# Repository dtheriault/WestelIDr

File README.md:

# WestelIDr
Westel Repeater Controller

This repository contains eagle files and arduino sketch files supporting a repeater
controller based on a Teensy3.2 chip.

The hardware was originally designed to support a Westel DRB25 repeater for WB7NFX
and then updated to support the K7YCA ARES/RACES team who also had one of these
machines.  The controller hardware while supporting the Westel repeater should be
easily modified for other repeater types.  It requires +12v @ approx 150ma, PTT,
Microphone and line audio to generate simple software based carrier detect.

The controller will generate a CW ID or Voice ID in the latest revision of the
sketch file for k7yca.  Can be operated in Ham or Commercial mode with different
timeouts.

Eagle files contain schematics and PCB layout supporting a 3 channel mixer and 3
transistor simplistic audio amplifier to drive a speaker mounted on the Westel
repeater.  There's Gerber files available to spin your own board.

NOTE IMPORTANT:  Current major pin-out issue with the voice ID chip.  I'll update
files and new layout once I fix the darn chip library file.

There's also some mechanical files for a mounting plate for the Westel repeater
which were contributed by Rob KG7LMI.

CW ID code was made possible by SV1DJG and very much appreciated for allowing me to
include his software in the sketch files.

For latest software please refer to the Sketch/k7yca/k7yca.ino file as this version
matches the hardware.  The other two versions were for earlier revisions of the
board for WB7NFX and our Sheriff's Jeep Posse team where I used the controller in
an AmmoCan portable repeater I built for them.

Contact info:

email:  no1d.doug@gmail.com
repository:  https://github.com/dtheriault/WestelIDr

 License:

 Copyright (C) 2017 Douglas Theriault - NO1D

 Software is free software: you can redistribute it and/or modify
 it under the terms of the GNU General Public License as published by
 the Free Software Foundation, either version 3 of the License, or
 (at your option) any later version.

 This is distributed in the hope that it will be useful to someone or ham club/group,
 but WITHOUT ANY WARRANTY; without even the implied warranty of MERCHANTABILITY
 or FITNESS FOR A PARTICULAR PURPOSE.  See the GNU General Public License for
 more details.

 You should have received a copy of the GNU General Public License
 in the repository.  If not, see <http://www.gnu.org/licenses/>.

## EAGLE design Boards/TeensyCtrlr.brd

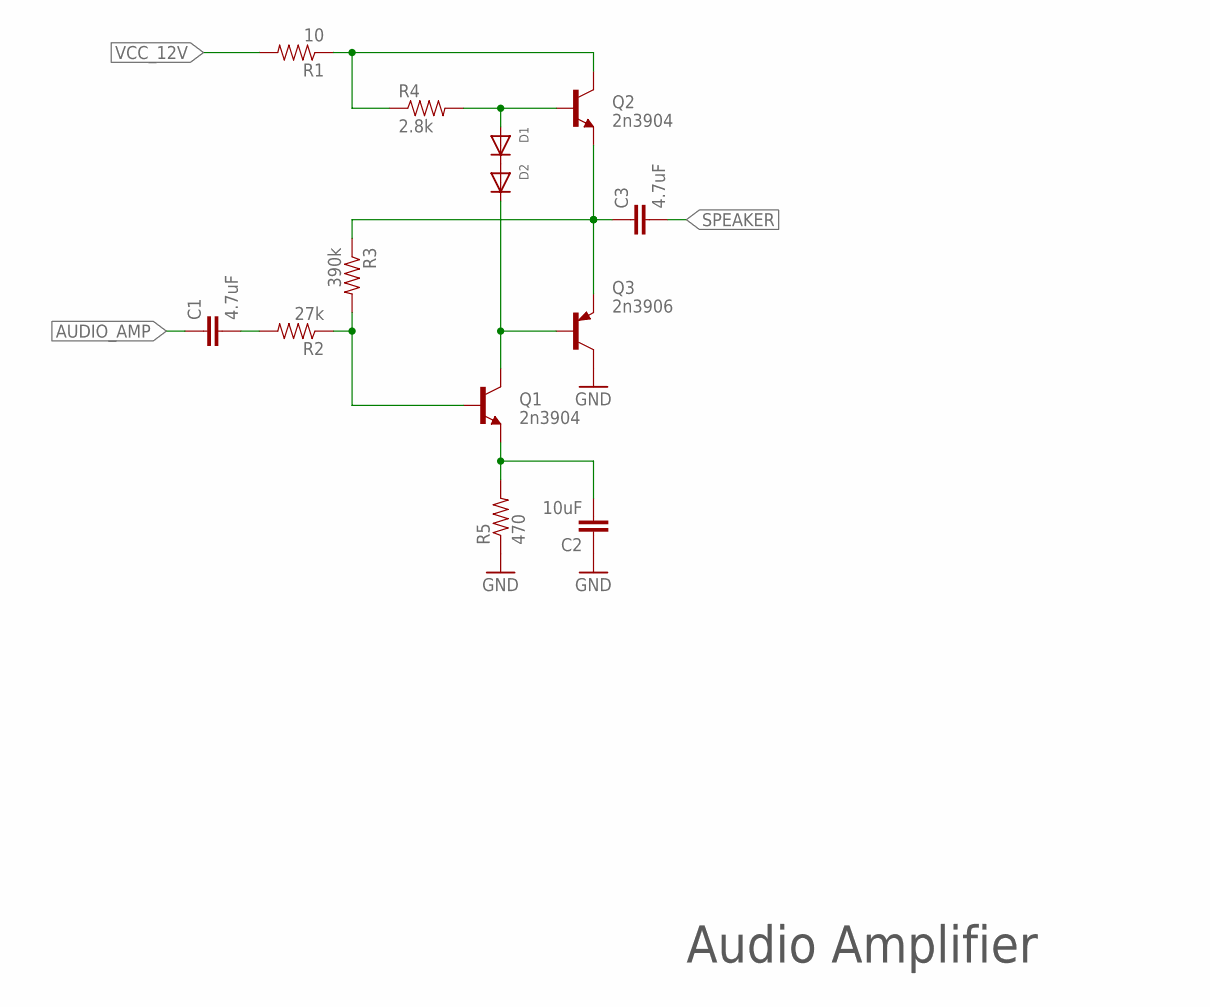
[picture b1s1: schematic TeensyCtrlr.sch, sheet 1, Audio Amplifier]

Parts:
C1, C3: 4.7uF; CAP-PTH-SMALL
C2: 10uF; CAP-PTH-SMALL
D1, D2: DIODEDO-1N4148; DO-1N4148
Q1, Q2: 2n3904; TO-92-AMMO
Q3: 2n3906; TO92-EBC
R1: 10; 0805
R2: 27k; 0805
R3: 390k; 0805
R4: 2.8k; 0805
R5: 470; 0805

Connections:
AUDIO_AMP: C1.1; also elsewhere on the board
GND: C2.1, Q3.C, R5.1; also elsewhere on the board
unnamed: C1.2, R2.2
unnamed: Q2.3 (C), R1.1, R4.1
unnamed: C2.2, Q1.1 (E), R5.2
unnamed: C3.1, Q2.1 (E), Q3.E, R3.1
unnamed: D1.C, D2.A
unnamed: D1.A, Q2.2 (B), R4.2
unnamed: D2.C, Q1.3 (C), Q3.B
unnamed: Q1.2 (B), R2.1, R3.2
SPEAKER: C3.2; also elsewhere on the board
VCC_12V: R1.2; also elsewhere on the board

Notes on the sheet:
Audio Amplifier

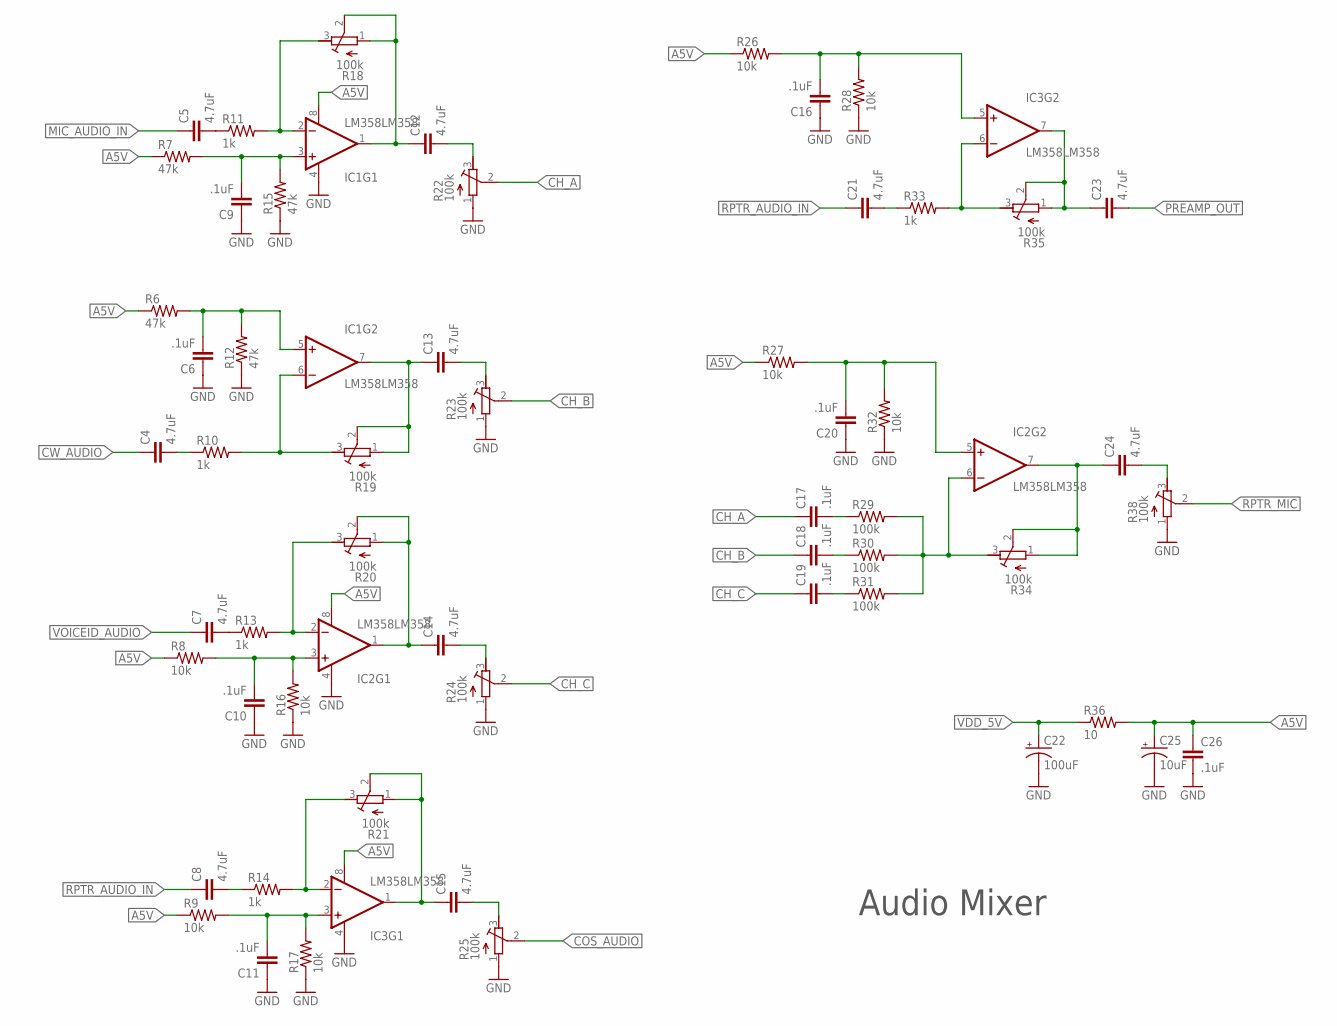
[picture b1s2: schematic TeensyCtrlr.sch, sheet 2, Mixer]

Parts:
C4, C5, C7, C8, C12, C13, C14, C15, C21, C23, C24: 4.7uF; CAP-PTH-SMALL2
C6, C9, C10, C11, C16, C17, C18, C19, C20, C26: .1uF; 0805
C22: 100uF; CPOL-RADIAL-10UF-25V
C25: 10uF; CPOL-RADIAL-100UF-25V
IC1, IC2, IC3: LM358LM358; SOIC8
R6, R7, R12, R15: 47k; 0805
R8, R9, R16, R17, R26, R27, R28, R32: 10k; 0805
R10, R11, R13, R14, R33: 1k; 0805
R18, R19, R20, R21, R22, R23, R24, R25, R34, R35, R38: 100k; RTRIM3296X
R29, R30, R31: 100k; 0805
R36: 10; 0805

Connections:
A5V: C25.1 (+), C26.1, IC1.8 (V+), IC2.8 (V+), IC3.8 (V+), R6.1, R7.1, R8.1, R9.1, R26.1, R27.1, R36.2
CH_A: C17.1, R22.2 (S)
CH_B: C18.1, R23.2 (S)
CH_C: C19.1, R24.2 (S)
COS_AUDIO: R25.2 (S); also elsewhere on the board
CW_AUDIO: C4.1; also elsewhere on the board
GND: C6.1, C9.1, C10.1, C11.1, C16.1, C20.1, C22.2 (-), C25.2 (-), C26.2, IC1.4 (V-), IC2.4 (V-), IC3.4 (V-), R12.1, R15.1, R16.1, R17.1, R22.1 (A), R23.1 (A), R24.1 (A), R25.1 (A), R28.1, R32.1, R38.1 (A); also elsewhere on the board
MIC_AUDIO_IN: C5.1; also elsewhere on the board
unnamed: IC1.2 (-IN), R11.2, R18.3 (E)
unnamed: C9.2, IC1.3 (+IN), R7.2, R15.2
unnamed: C5.2, R11.1
unnamed: C12.1, IC1.1 (OUT), R18.1 (A), R18.2 (S)
unnamed: C12.2, R22.3 (E)
unnamed: IC1.6 (-IN), R10.2, R19.3 (E)
unnamed: C6.2, IC1.5 (+IN), R6.2, R12.2
unnamed: C4.2, R10.1
unnamed: C13.1, IC1.7 (OUT), R19.1 (A), R19.2 (S)
unnamed: C13.2, R23.3 (E)
unnamed: IC2.2 (-IN), R13.2, R20.3 (E)
unnamed: C10.2, IC2.3 (+IN), R8.2, R16.2
unnamed: C7.2, R13.1
unnamed: C14.1, IC2.1 (OUT), R20.1 (A), R20.2 (S)
unnamed: C14.2, R24.3 (E)
unnamed: IC2.6 (-IN), R29.2, R30.2, R31.2, R34.3 (E)
unnamed: C20.2, IC2.5 (+IN), R27.2, R32.2
unnamed: C24.1, IC2.7 (OUT), R34.1 (A), R34.2 (S)
unnamed: C24.2, R38.3 (E)
unnamed: IC3.2 (-IN), R14.2, R21.3 (E)
unnamed: C11.2, IC3.3 (+IN), R9.2, R17.2
unnamed: C8.2, R14.1
unnamed: C15.1, IC3.1 (OUT), R21.1 (A), R21.2 (S)
unnamed: C15.2, R25.3 (E)
unnamed: IC3.6 (-IN), R33.2, R35.3 (E)
unnamed: C16.2, IC3.5 (+IN), R26.2, R28.2
unnamed: C21.2, R33.1
unnamed: C23.1, IC3.7 (OUT), R35.1 (A), R35.2 (S)
unnamed: C17.2, R29.1
unnamed: C18.2, R30.1
unnamed: C19.2, R31.1
PREAMP_OUT: C23.2; also elsewhere on the board
RPTR_AUDIO_IN: C8.1, C21.1; also elsewhere on the board
RPTR_MIC: R38.2 (S); also elsewhere on the board
VDD_5V: C22.1 (+), R36.1; also elsewhere on the board
VOICEID_AUDIO: C7.1; also elsewhere on the board

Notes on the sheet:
Audio Mixer

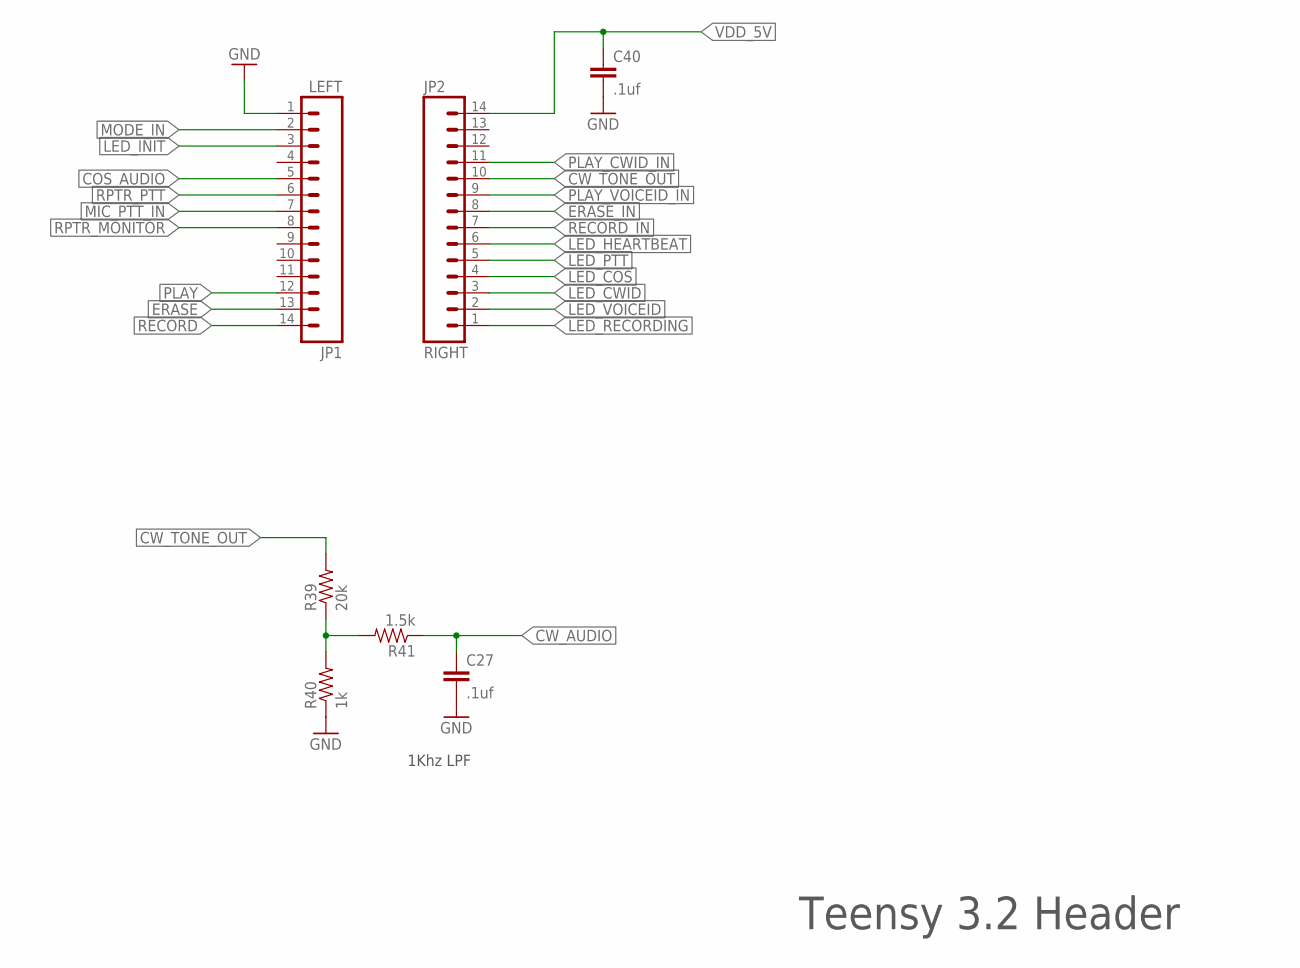
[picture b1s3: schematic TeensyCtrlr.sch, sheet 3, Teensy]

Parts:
C27, C40: .1uf; 0805
JP1: LEFT; 1X14-LONGPADS
JP2: RIGHT; 1X14-LONGPADS
R39: 20k; 0805
R40: 1k; 0805
R41: 1.5k; 0805

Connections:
COS_AUDIO: JP1.5; also elsewhere on the board
CW_AUDIO: C27.1, R41.1; also elsewhere on the board
CW_TONE_OUT: JP2.10, R39.2
ERASE: JP1.13; also elsewhere on the board
ERASE_IN: JP2.8; also elsewhere on the board
GND: C27.2, C40.2, JP1.1, R40.1; also elsewhere on the board
LED_COS: JP2.4; also elsewhere on the board
LED_CWID: JP2.3; also elsewhere on the board
LED_HEARTBEAT: JP2.6; also elsewhere on the board
LED_INIT: JP1.3; also elsewhere on the board
LED_PTT: JP2.5; also elsewhere on the board
LED_RECORDING: JP2.1; also elsewhere on the board
LED_VOICEID: JP2.2; also elsewhere on the board
MIC_PTT_IN: JP1.7; also elsewhere on the board
MODE_IN: JP1.2; also elsewhere on the board
unnamed: R39.1, R40.2, R41.2
PLAY: JP1.12; also elsewhere on the board
PLAY_CWID_IN: JP2.11; also elsewhere on the board
PLAY_VOICEID_IN: JP2.9; also elsewhere on the board
RECORD: JP1.14; also elsewhere on the board
RECORD_IN: JP2.7; also elsewhere on the board
RPTR_MONITOR: JP1.8; also elsewhere on the board
RPTR_PTT: JP1.6; also elsewhere on the board
VDD_5V: C40.1, JP2.14; also elsewhere on the board

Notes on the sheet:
Teensy 3.2 Header
1Khz LPF

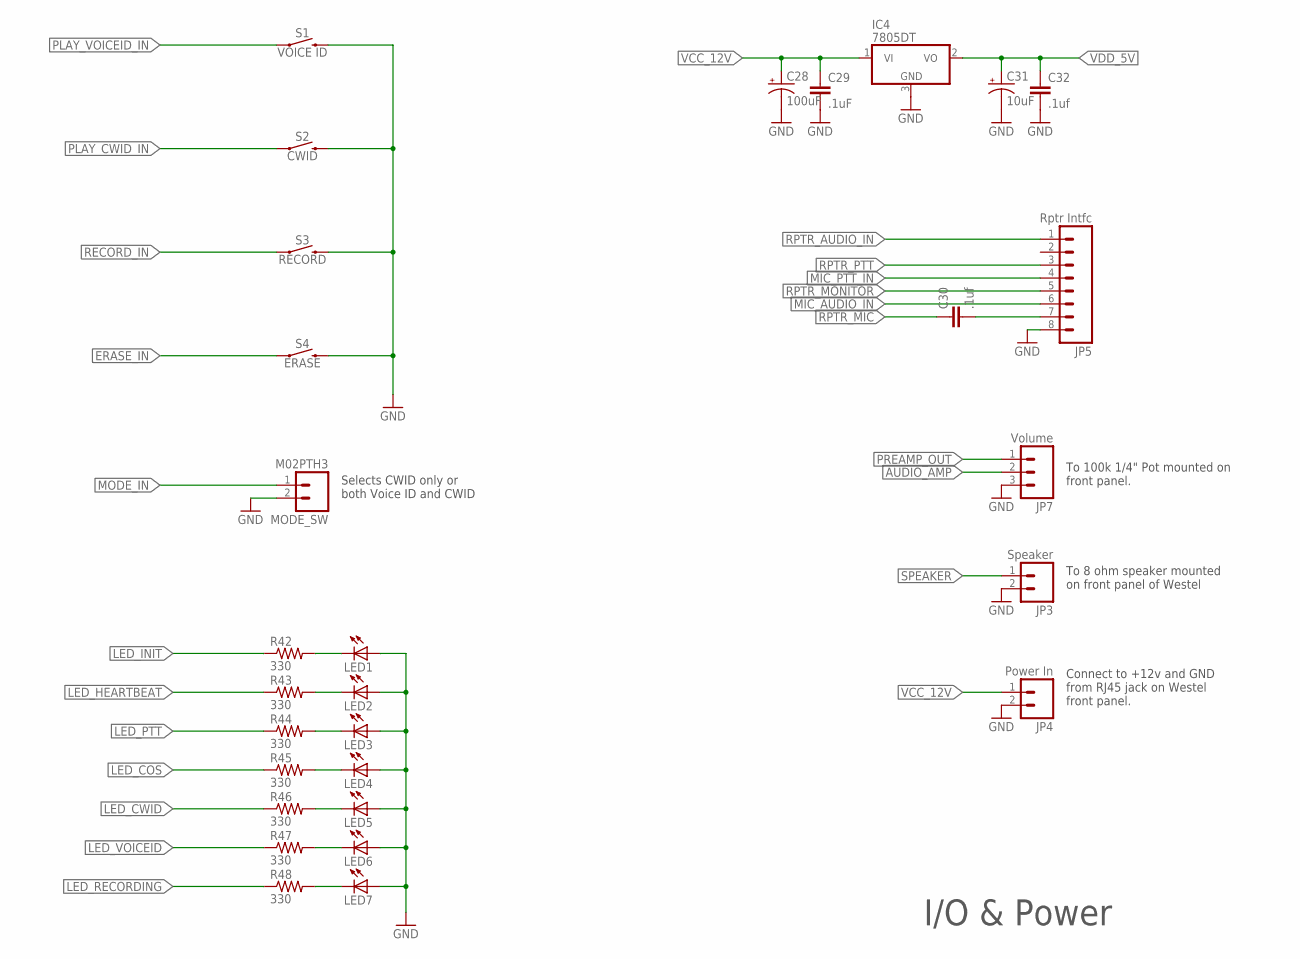
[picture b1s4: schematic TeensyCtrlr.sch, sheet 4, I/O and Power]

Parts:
C28: 100uF; CPOL-RADIAL-1000UF-25V
C29: .1uF; 0805
C30, C32: .1uf; 0805
C31: 10uF; CPOL-RADIAL-100UF-25V
IC4: 7805DT; TO252
JP3: Speaker; 1X02_LONGPADS
JP4: Power In; 1X02_LONGPADS
JP5: Rptr Intfc; 1X08_LONGPADS
JP7: Volume; 1X03_LONGPADS
LED1, LED2, LED3, LED4, LED5, LED6, LED7: LED5MM
MODE_SW: M02PTH3; 1X02_LONGPADS
R42, R43, R44, R45, R46, R47, R48: 330; 0805
S1: VOICE ID; TACTILE_SWITCH_PTH_6.0MM
S2: CWID; TACTILE_SWITCH_PTH_6.0MM
S3: RECORD; TACTILE_SWITCH_PTH_6.0MM
S4: ERASE; TACTILE_SWITCH_PTH_6.0MM

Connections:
AUDIO_AMP: JP7.2; also elsewhere on the board
ERASE_IN: S4.1; also elsewhere on the board
GND: C28.-, C29.2, C31.2 (-), C32.2, IC4.3 (GND), JP3.2, JP4.2, JP5.8, JP7.3, LED1.A, LED2.A, LED3.A, LED4.A, LED5.A, LED6.A, LED7.A, MODE_SW.2, S1.3 (2), S2.3 (2), S3.3 (2), S4.3 (2); also elsewhere on the board
LED_COS: R45.1; also elsewhere on the board
LED_CWID: R46.1; also elsewhere on the board
LED_HEARTBEAT: R43.1; also elsewhere on the board
LED_INIT: R42.1; also elsewhere on the board
LED_PTT: R44.1; also elsewhere on the board
LED_RECORDING: R48.1; also elsewhere on the board
LED_VOICEID: R47.1; also elsewhere on the board
MIC_AUDIO_IN: JP5.6; also elsewhere on the board
MIC_PTT_IN: JP5.4; also elsewhere on the board
MODE_IN: MODE_SW.1; also elsewhere on the board
unnamed: LED1.K (C), R42.2
unnamed: LED2.K (C), R43.2
unnamed: LED3.K (C), R44.2
unnamed: LED4.K (C), R45.2
unnamed: LED5.K (C), R46.2
unnamed: LED6.K (C), R47.2
unnamed: LED7.K (C), R48.2
unnamed: C30.2, JP5.7
PLAY_CWID_IN: S2.1; also elsewhere on the board
PLAY_VOICEID_IN: S1.1; also elsewhere on the board
PREAMP_OUT: JP7.1; also elsewhere on the board
RECORD_IN: S3.1; also elsewhere on the board
RPTR_AUDIO_IN: JP5.1; also elsewhere on the board
RPTR_MIC: C30.1; also elsewhere on the board
RPTR_MONITOR: JP5.5; also elsewhere on the board
RPTR_PTT: JP5.3; also elsewhere on the board
SPEAKER: JP3.1; also elsewhere on the board
VCC_12V: C28.+, C29.1, IC4.1 (VI), JP4.1; also elsewhere on the board
VDD_5V: C31.1 (+), C32.1, IC4.2 (VO); also elsewhere on the board

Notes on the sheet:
I/O & Power
To 100k 1/4" Pot mounted on front panel.
To 8 ohm speaker mounted on front panel of Westel
Connect to +12v and GND from RJ45 jack on Westel front panel.
Selects CWID only or both Voice ID and CWID

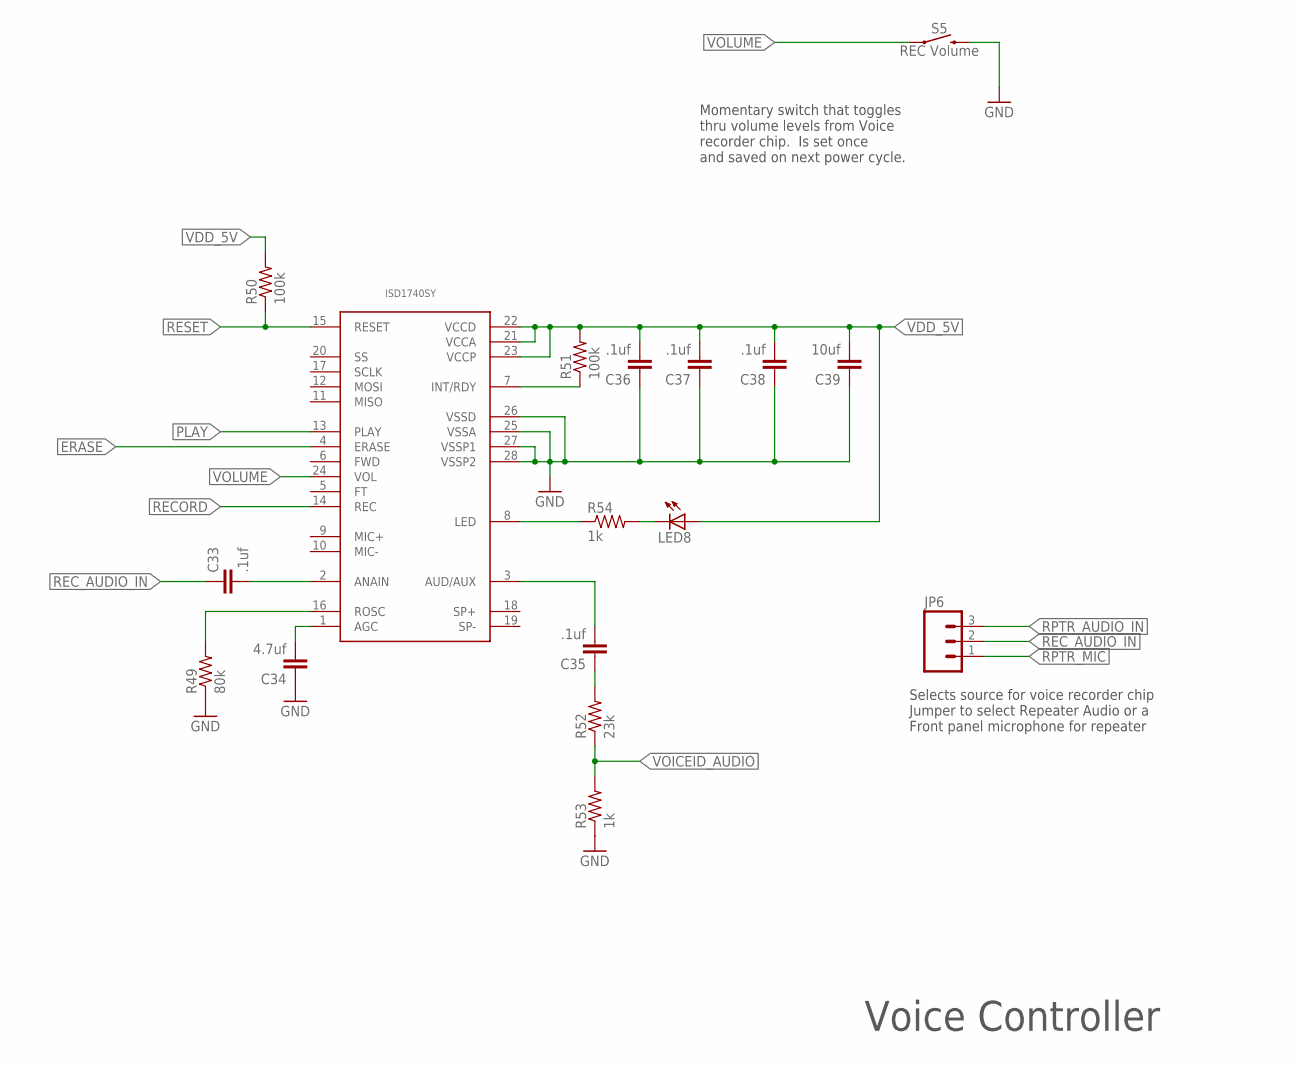
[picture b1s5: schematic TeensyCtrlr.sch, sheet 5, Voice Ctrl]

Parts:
C33, C35, C36, C37, C38: .1uf; 0805
C34: 4.7uf; 0805
C39: 10uf; 0805
IC$1: ISD1740SYSOIC28; SOIC-28
JP6: M03LONGPADS; 1X03_LONGPADS
LED8: LEDCHIP-LED0805; CHIP-LED0805
R49: 80k; 0805
R50, R51: 100k; 0805
R52: 23k; 0805
R53, R54: 1k; 0805
S5: REC Volume; TACTILE_SWITCH_PTH_6.0MM

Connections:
ERASE: IC$1.4 (ERASE); also elsewhere on the board
GND: C34.1, C36.1, C37.1, C38.1, C39.1, IC$1.25 (VSSA), IC$1.26 (VSSD), IC$1.27 (VSSP1), IC$1.28 (VSSP2), R49.1, R53.1, S5.3 (2); also elsewhere on the board
unnamed: C33.2, IC$1.2 (ANAIN)
unnamed: C35.2, IC$1.3 (AUD/AUX)
unnamed: C35.1, R52.2
unnamed: C34.2, IC$1.1 (AGC)
unnamed: IC$1.16 (ROSC), R49.2
unnamed: IC$1.7 (INT/RDY), R51.1
unnamed: IC$1.8 (LED), R54.1
unnamed: LED8.C, R54.2
PLAY: IC$1.13 (PLAY); also elsewhere on the board
RECORD: IC$1.14 (REC); also elsewhere on the board
REC_AUDIO_IN: C33.1, JP6.2
RESET: IC$1.15 (RESET), R50.1
RPTR_AUDIO_IN: JP6.3; also elsewhere on the board
RPTR_MIC: JP6.1; also elsewhere on the board
VDD_5V: C36.2, C37.2, C38.2, C39.2, IC$1.21 (VCCA), IC$1.22 (VCCD), IC$1.23 (VCCP), LED8.A, R50.2, R51.2; also elsewhere on the board
VOICEID_AUDIO: R52.1, R53.2; also elsewhere on the board
VOLUME: IC$1.24 (VOL), S5.1

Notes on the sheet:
Voice Controller
Selects source for voice recorder chip Jumper to select Repeater Audio or a Front panel microphone for repeater
Momentary switch that toggles thru volume levels from Voice recorder chip. Is set once and saved on next power cycle.

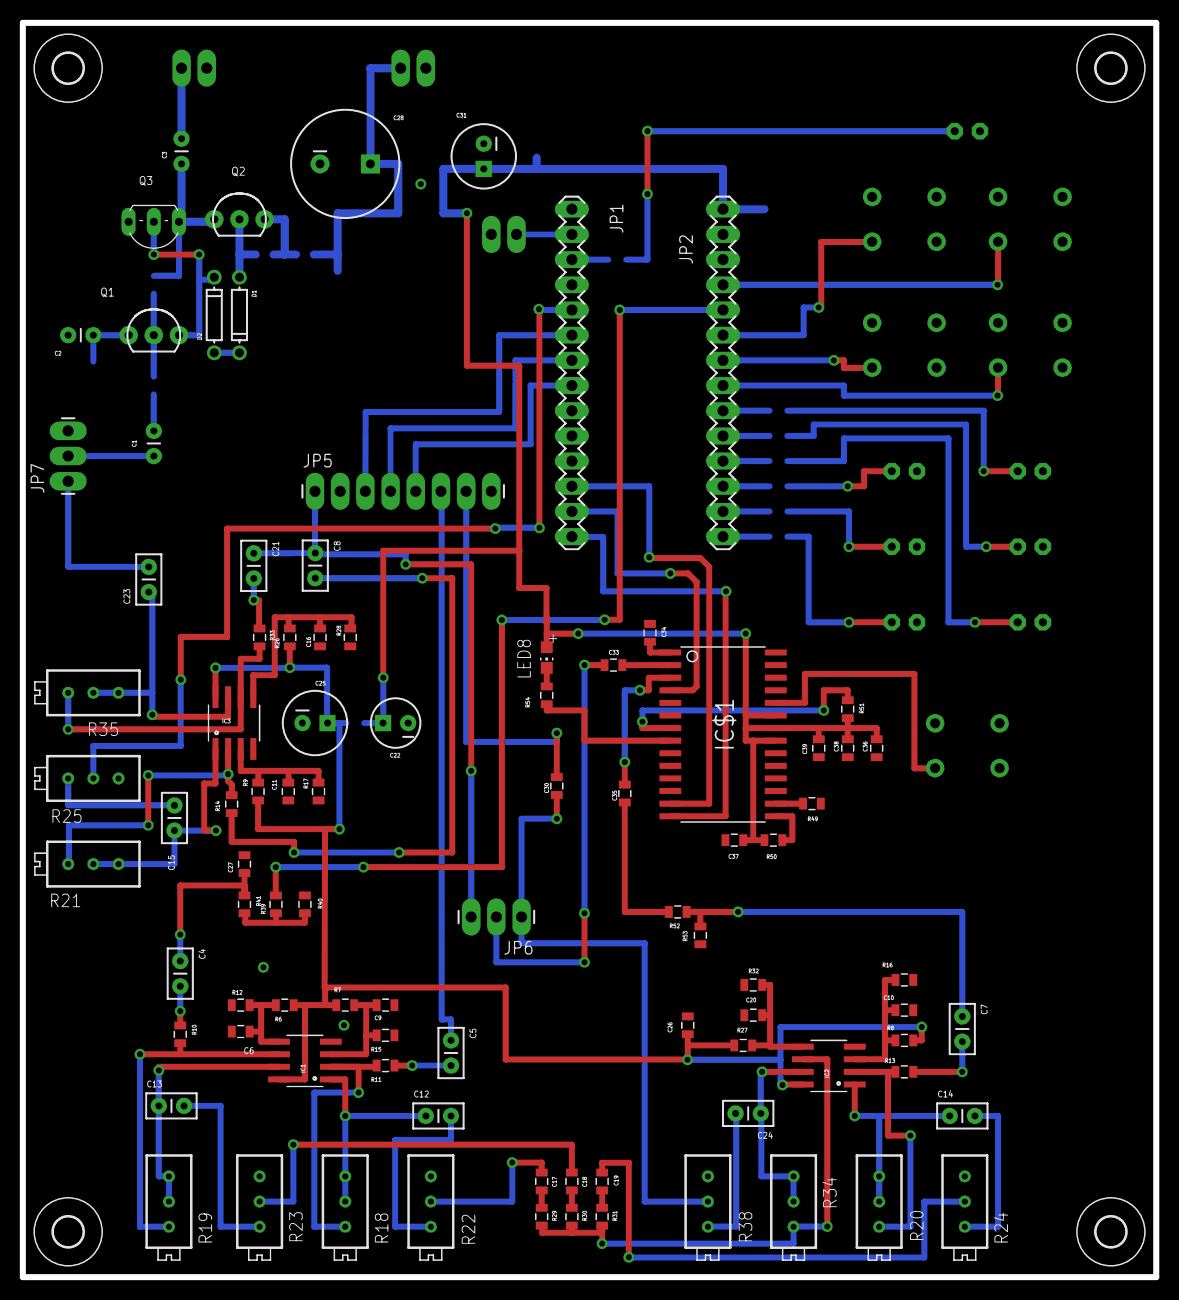
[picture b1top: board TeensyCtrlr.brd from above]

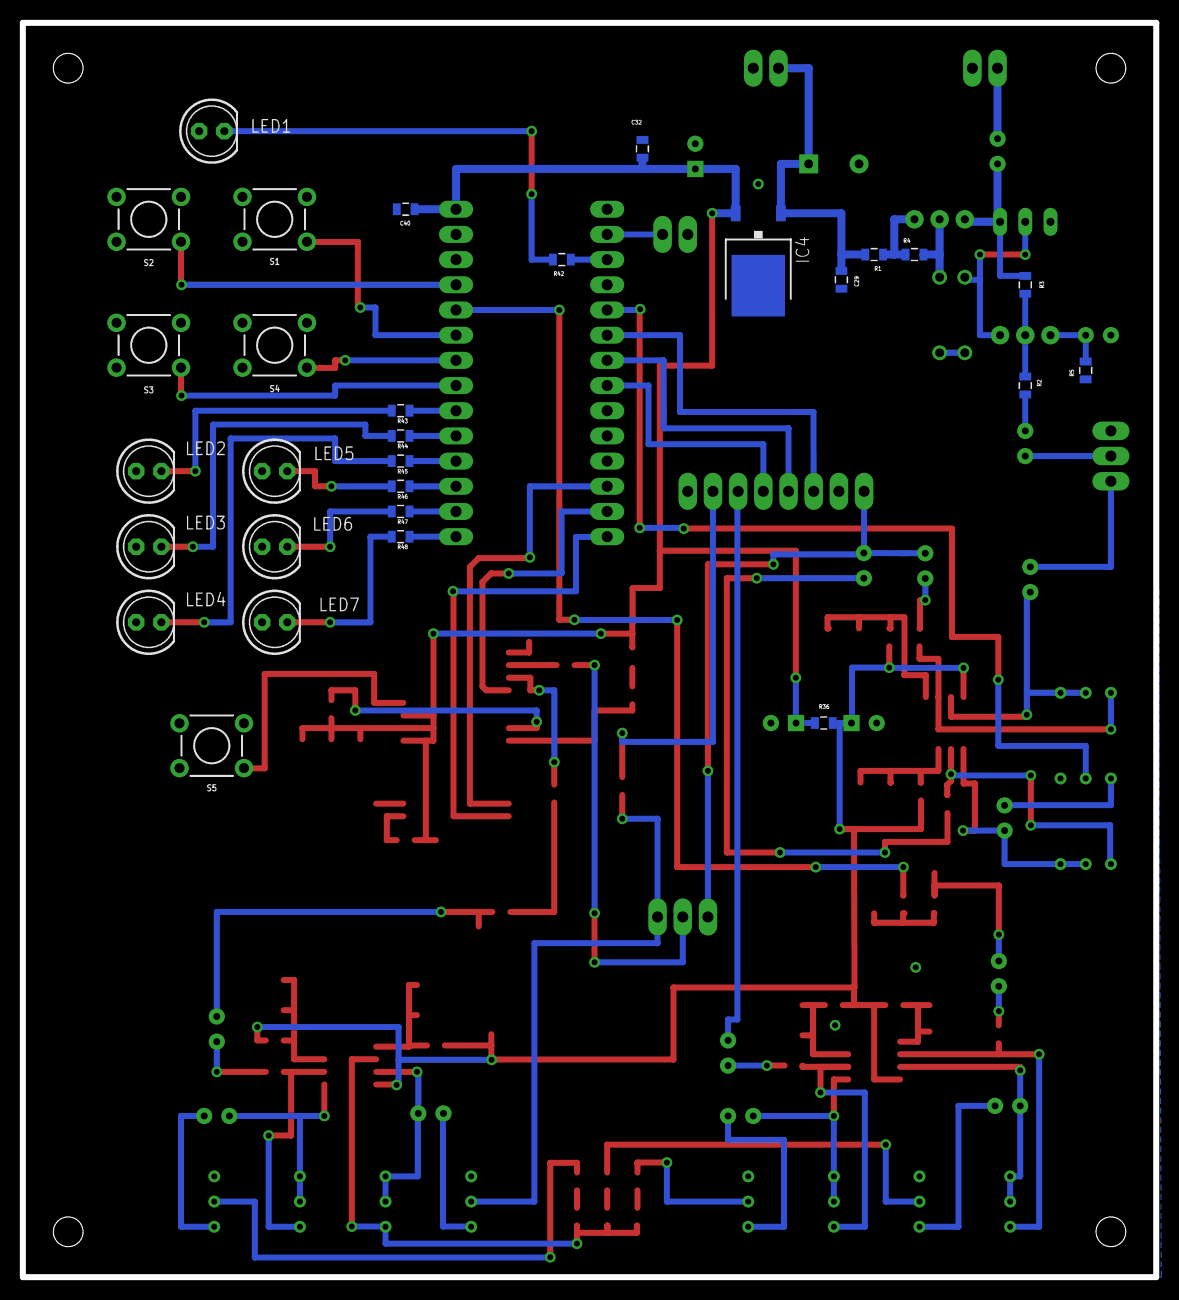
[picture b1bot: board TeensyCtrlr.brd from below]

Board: 2 copper layers, 114.3 x 126.5 mm, 128 parts (29 on the bottom side), 94 nets.

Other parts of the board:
U$1, U$2, U$3, U$4: 3,0

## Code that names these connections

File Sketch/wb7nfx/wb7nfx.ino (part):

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//
// PIN Definitions:  Input and Outputs
//
#define PLAY_VOICE_IN  1          // Send the Voice ID, Play on Voice Bd
#define PLAY_CW_IN     2          // Send a CW ID from the Teensy
#define ERASE_IN       3          // Erase the Voice ID, Erase on Voice Bd
#define RECORD_IN      4          // Record New Voice ID, Record on Voice Bd
#define MODE_IN        5          // Toggle switch for CW only or CW & Voice ID
//
#define LED_INIT       6          // Setup has been executed, stays lit
#define LED_HEARTBEAT  7          // Loop interval, one second pulse
#define LED_PTT        8          // PTT is activated, Microphone front panel
#define LED_COS        9          // COS detected from Repeater Audio feed
#define LED_CWID      10          // CW ID in process
#define LED_VOICEID   11          // Voice ID in process
#define LED_RECORDING 12          // Recording new Voice ID in process
//
#define RPTR_MONITOR  14          // Repeater Monitor Active Low (not used)
#define PTT_IN        15          // Front Panel Microphone, Active Low
//
#define RECORD_OUT    18          // Button on Voice Bd
#define ERASE_OUT     19          // Button on Voice Bd
#define PLAY_OUT      20          // Button on Voice Bd
//
#define CW_AUDIO      21          // PWM Teensy output of CW Audio tone
#define PTT_OUT       22          // PTT to Repeater, Active Low
#define COS_IN        23          // Carrier Detect Input
//
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//
#define CW_TONE      750          // CW ID Tone in Hertz
//
#define MODE_CW_ONLY   0          // Does not play Voice ID
#define MODE_BOTH      1          // Plays both Voice and CW ID's
//
// State Machine Defines
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//
// Timeouts are in seconds
//
#define CW_TIMEOUT    600         // Play CW ID every 10m after COS or PTT go active
#define VOICE_TIMEOUT 1800        // Play Voice ID every 30m when IDLE
#define COS_TIMEOUT   300         // COS/PTT 3m timeout
#define VID_TIMEOUT   1200        // 20m after CWID, if we're idle, we VoiceID
//
// All delays are in ms
//
#define RECORDING_DELAY 8000      // Record for 8s
#define ERASE_DELAY     10000     // Erase for 10s
#define VOICEID_DELAY   7000      // 7s for voice id to play
#define PTT_DELAY       750       // 1.5s PTT delay 
#define COS_DELAY       100       // delay 100ms between consecutive COS ADC reads
//
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  pinMode(PTT_IN, INPUT_PULLUP);
  pinMode(PLAY_VOICE_IN, INPUT_PULLUP);
  pinMode(PLAY_CW_IN, INPUT_PULLUP);
  pinMode(ERASE_IN, INPUT_PULLUP);
  pinMode(RECORD_IN, INPUT_PULLUP);
  pinMode(MODE_IN, INPUT_PULLUP);

  analogReference(DEFAULT);
  for (x = 0; x < 100; x++) {
    value += analogRead(COS_IN);
  }
  
  pinMode(LED_INIT, OUTPUT);
  pinMode(LED_HEARTBEAT, OUTPUT);
  pinMode(LED_PTT, OUTPUT);
  pinMode(LED_COS, OUTPUT);
  pinMode(LED_CWID, OUTPUT);
  pinMode(LED_VOICEID, OUTPUT);
  pinMode(LED_RECORDING, OUTPUT);

  // pinMode(CW_AUDIO, ????);

  pinMode(PTT_OUT, OUTPUT);
  pinMode(PLAY_OUT, OUTPUT);
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
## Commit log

2017-06-02 1. Re-aligned lower right hole to match lower left 2. Locked all holes, LED's and switches 3. Added bit more clearance in DRC rules 4. Reset trace widths to .024 5. DRC rules checks passing except fo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
2017-06-02 1. Forgot to reverse LED 1, same position, re-locked it 2. Fixed few trace alignments and un-routed grounds
2017-06-03 Checkin of faceplate Sketchup files and Simplify 3D printing profile (not yet updated for latest version)
2017-06-11 Add 0.9.2 revised version: - deepen embossed text (also change print settings to print the first 3 layers at 0-.2mm Z resolution) - move right side faceplate mounting holes to the left by 0.5mm
2017-06-11 Add Simplify 3D factory file: print first 4 layers at 0.2 to improve embedded text resolution, then switch to 0.4mm layers for the remainder of the print
2017-06-14 0.9.3 changes: 1. move speaker down to clear the card support rail 2. move the standoffs for the PCB down a bit to add clearance between the speaker and the board (not needed, but just in case ...)
2017-07-03 Minor layout change (no holes/dimension changes) Generated Gerber files for test run at Seeed Studio Generated some .ps files Top and Bot layers for in house board generation
2017-07-20 Latest controller sketch files
2017-07-20 Updated board files for Seeed Fusion board run. Please note that the Voice ID chip layout is totally wrong. Prototype required dead-bug fix with ~27 wires. Will push a fix to the board layout in abou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
2017-07-21 Remove old files and replace with (hopefully) final Sketchup, STL, and Simplify 3D factory files
2017-08-10 Initial version deployed on Mingus. There's still a bug that exists where CWID will generate a double ID. Believe due to not waiting 10m after going into IDLE state as next COR causes change into ID_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
2017-08-10 Fixed double ID problem by not entering ID_FIRST state from IDLE unless last_id timer has exceeded the CW or Voice ID timer. Tested in Ham mode but still needs to be checked in Commercial mode.
    Cleaned up comments and references.
2017-08-10 Update to README.md file

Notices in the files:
parts and their libraries:
SparkFun-Capacitors: Licensing: Creative Commons ShareAlike 4.0 International - https://creativecommons.org/licenses/by-sa/4.0
